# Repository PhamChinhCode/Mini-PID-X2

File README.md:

# Mini PID X2

Board điều khiển 2 động cơ DC chổi than có encoder, chạy vòng PID trên STM32F103C8T6. Thiết kế bằng **KiCad 10**, kích thước **55 × 40 mm**.

## Hình ảnh

| Mặt trên | Mặt dưới |
|---|---|
|  |  |

Mặt dưới có các pad test được in tên: SWD (3V3, DIO, CLK, GND), J8 (5V, CTL1–CTL3, GND) và chân của hai cổng động cơ M1/M2 (OUT1, GND, ENA, ENB, 3V3, OUT2).

## Tính năng

- Điều khiển **2 động cơ DC** bằng 2 × **DRV8871** (H-bridge tích hợp, giới hạn dòng bằng R_ILIM 22 kΩ).
- **2 kênh encoder A/B** với điện trở kéo lên 10 kΩ và bộ lọc RC (1 kΩ + 1 nF).
- MCU **STM32F103C8T6**, thạch anh 16 MHz, USB Full-Speed qua cổng **USB-C**.
- Nguồn vào **VIN** (pin 2S–4S, tối đa khoảng 18 V):
  - Chống cắm ngược cực bằng P-MOSFET **AONR21357**, gate được kẹp bằng Zener 10 V.
  - TVS **SMAJ18A** và tụ hóa 100 µF.
  - Cầu chia đo điện áp VIN đưa về ADC.
- **Buck 5 V MP2359** (1,2 A đỉnh, khuyến nghị tải ≤ 1 A), ghép OR bằng diode với VBUS của USB-C.
- **LDO 3,3 V ME6211** cho MCU và encoder.
- 3 ngõ vào điều khiển ngoài (J8), mỗi ngõ có LED báo trạng thái.
- Cổng UART, I2C và SWD riêng; nút RESET, BOOT0 và USER.

## Cấu trúc thư mục

| Đường dẫn | Nội dung |
|---|---|
| `MiniPID_Manual.kicad_pro` / `.kicad_sch` / `.kicad_pcb` | Project KiCad: schematic và PCB |
| `MiniPID_Manual.kicad_sym` | Thư viện symbol riêng của project (MP2359DJ) |
| `MiniPID_Manual.pretty/` | Thư viện footprint riêng |
| `BOM_MuaHang.csv` | Danh sách mua linh kiện đã gộp mã (32 mã, 89 linh kiện mỗi board), có mã LCSC |
| `bom/ibom.html` | Interactive BOM, mở bằng trình duyệt để hỗ trợ hàn |
| `gerber_to_order/` | Gerber nén zip để đặt mạch (JLCPCB, PCBWay, Elecrow, FusionPCB) |
| `images/` | Ảnh render 3D, mặt trên và mặt dưới của PCB |
| `tools/` | CLI `minipid` bọc `kicad-cli` và `pcbnew` (xem `tools/README.md`) |
| `legacy/` | Dữ liệu gốc từ EasyEDA Pro (file `.epro`, symbol và footprint đã import) |

## Connector

| Ref | Loại | Chân |
|---|---|---|
| J1 | Nguồn vào | 1 GND, 2 VIN |
| J2 / J3 | JST PH 6P, động cơ 1 / 2 | 1 OUT1, 2 GND, 3 ENC_A, 4 ENC_B, 5 +3V3, 6 OUT2 |
| J4 | USB-C | USB 2.0 FS, CC 5,1 kΩ (thiết bị) |
| J5 | PicoBlade 4P, UART | 1 +3V3, 2 TX, 3 RX, 4 GND |
| J6 | PicoBlade 4P, I2C | 1 GND, 2 +3V3, 3 SDA, 4 SCL |
| J7 | Header 2.54 mm 4P, SWD | 1 +3V3, 2 SWDIO, 3 SWCLK, 4 GND |
| J8 | JST PH 5P, điều khiển | 1 +5V, 2 CTL1, 3 CTL2, 4 CTL3, 5 GND |

> Encoder được cấp **3,3 V** từ J2/J3. Encoder Hall loại 5 V cần kiểm tra lại mức điện áp trước khi dùng.

## Mở và xuất file

```bash
kicad MiniPID_Manual.kicad_pro
```

```bash
kicad-cli sch erc MiniPID_Manual.kicad_sch
```

```bash
kicad-cli pcb drc --schematic-parity MiniPID_Manual.kicad_pcb
```

## Ghi chú thiết kế

- Buck đặt R4 = 51 kΩ, R5 = 10 kΩ, cho Vout ≈ 4,94 V. Sau diode OR, rail +5V còn khoảng 4,6 V.
- Đầu ra buck dùng tụ 10 µF 50 V × 2; datasheet MP2359 khuyên khoảng 22 µF.
- MP2359 đang ở trạng thái *Not recommended for new designs* (MPS khuyên chuyển sang MP2331H). Linh kiện vẫn có trên JLCPCB/LCSC: C14259, hoặc bản tương thích MSKSEMI C30197555.
- Gerber trong `gerber_to_order/` được xuất ngày 2026-11-08. Nên xuất lại từ PCB hiện tại trước khi đặt mạch.

## Việc còn tồn

- [ ] Lỗ bắt vít H1–H4 chưa gán net trong schematic (8 lỗi ERC).
- [ ] Đường GND trên F.Cu chạm pad H4 (DRC báo chập mạch và vi phạm khe hở).
- [ ] J1: mã LCSC là XT30PW nhưng footprint đang là terminal Phoenix 5.08 mm. Cần đổi mã LCSC cho đúng loại terminal block.
- [ ] R4 trong schematic/PCB đã đổi giá trị thành 51 kΩ nhưng trường LCSC/MPN vẫn là mã 49.9k (C23184). Mã đúng là C23196 / 0603WAF5102T5E (`BOM_MuaHang.csv` đã sửa).
- [ ] Silkscreen ghi "M1 Brigde" / "M2 Brigde", nên sửa thành "Bridge".

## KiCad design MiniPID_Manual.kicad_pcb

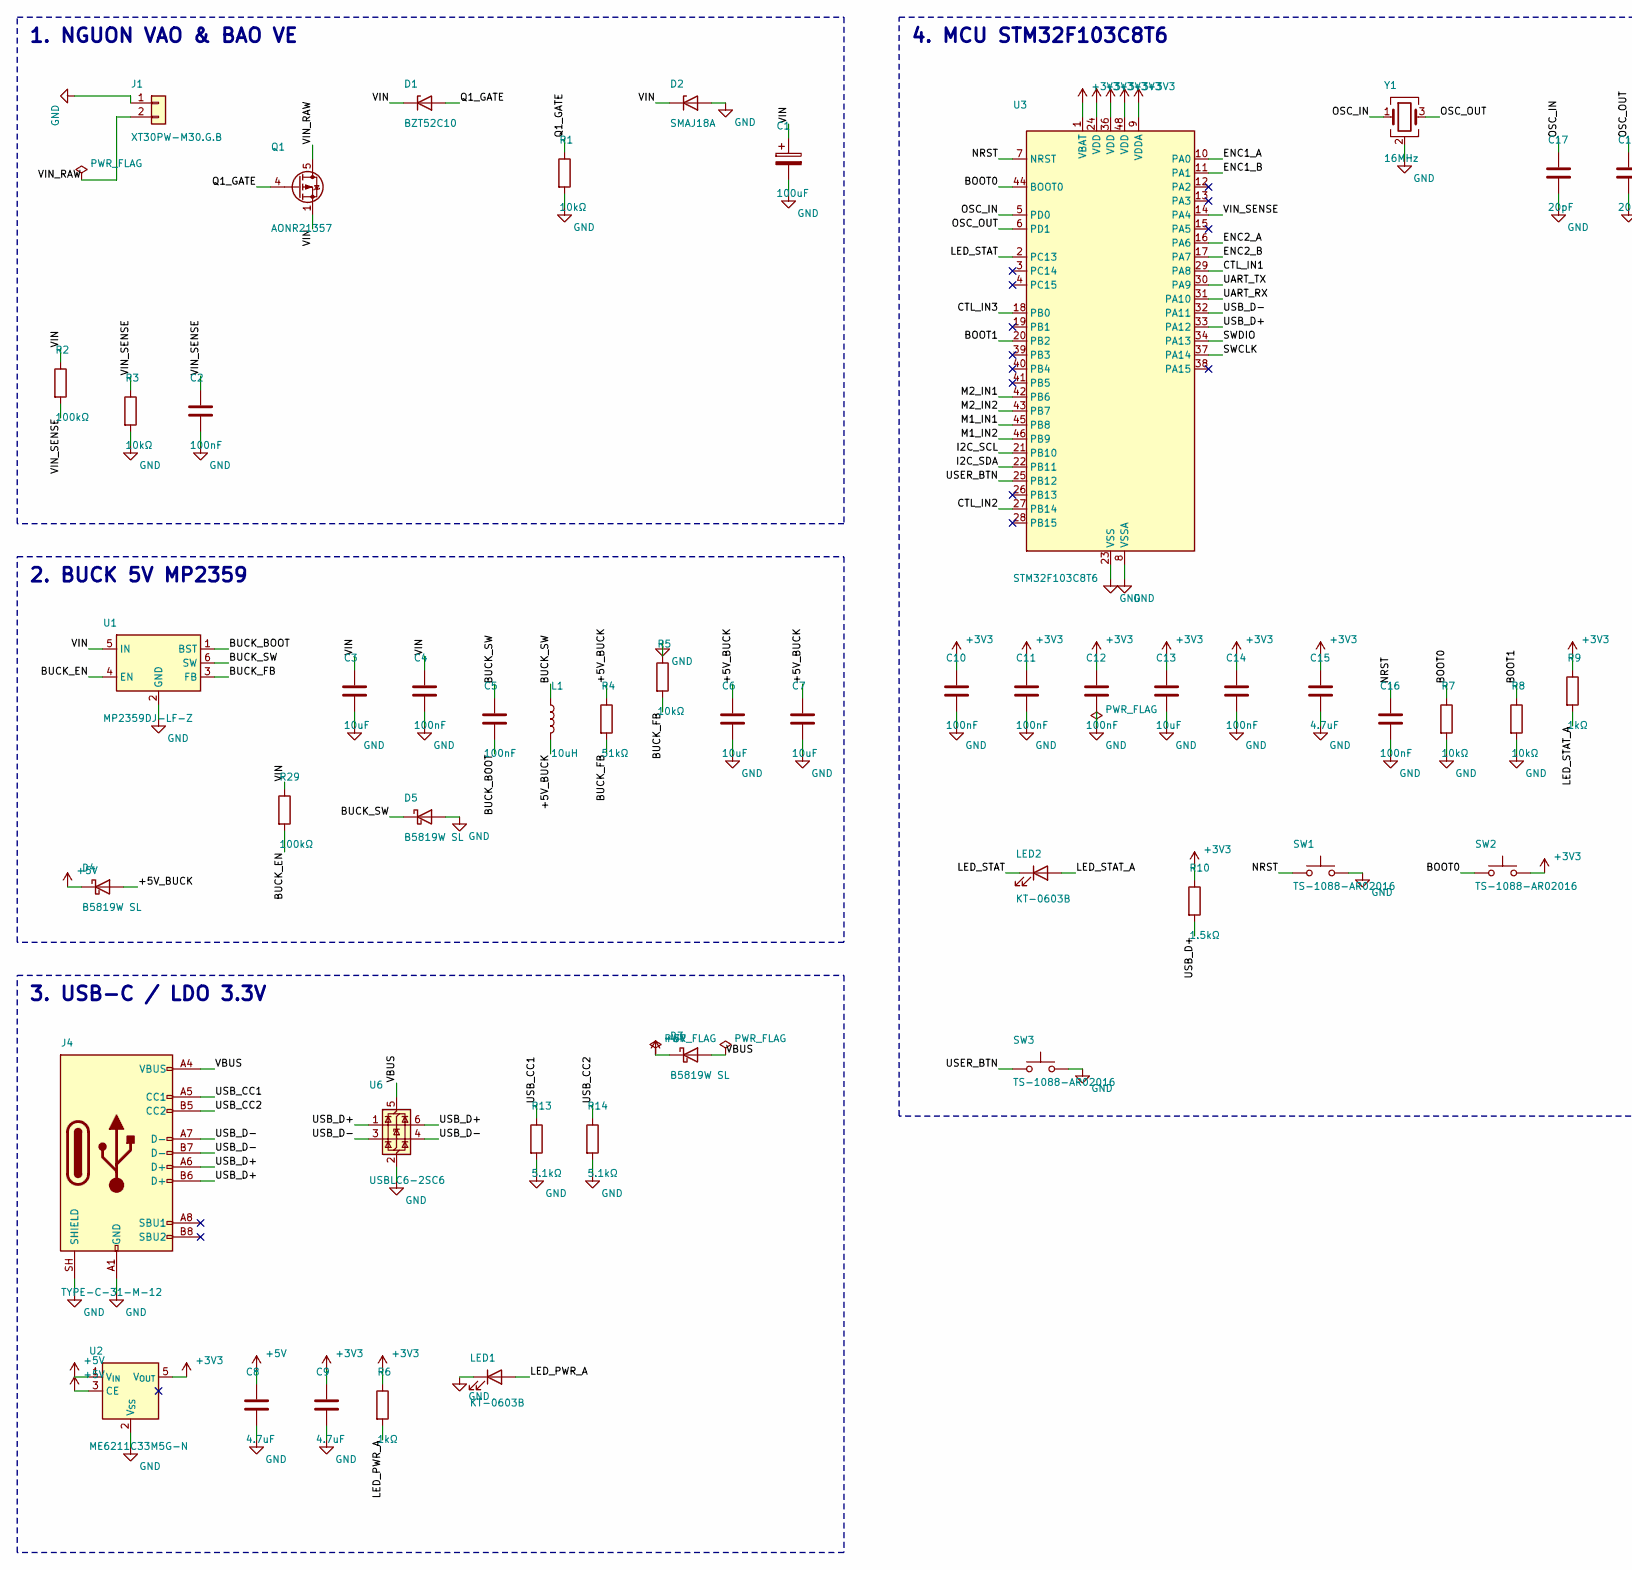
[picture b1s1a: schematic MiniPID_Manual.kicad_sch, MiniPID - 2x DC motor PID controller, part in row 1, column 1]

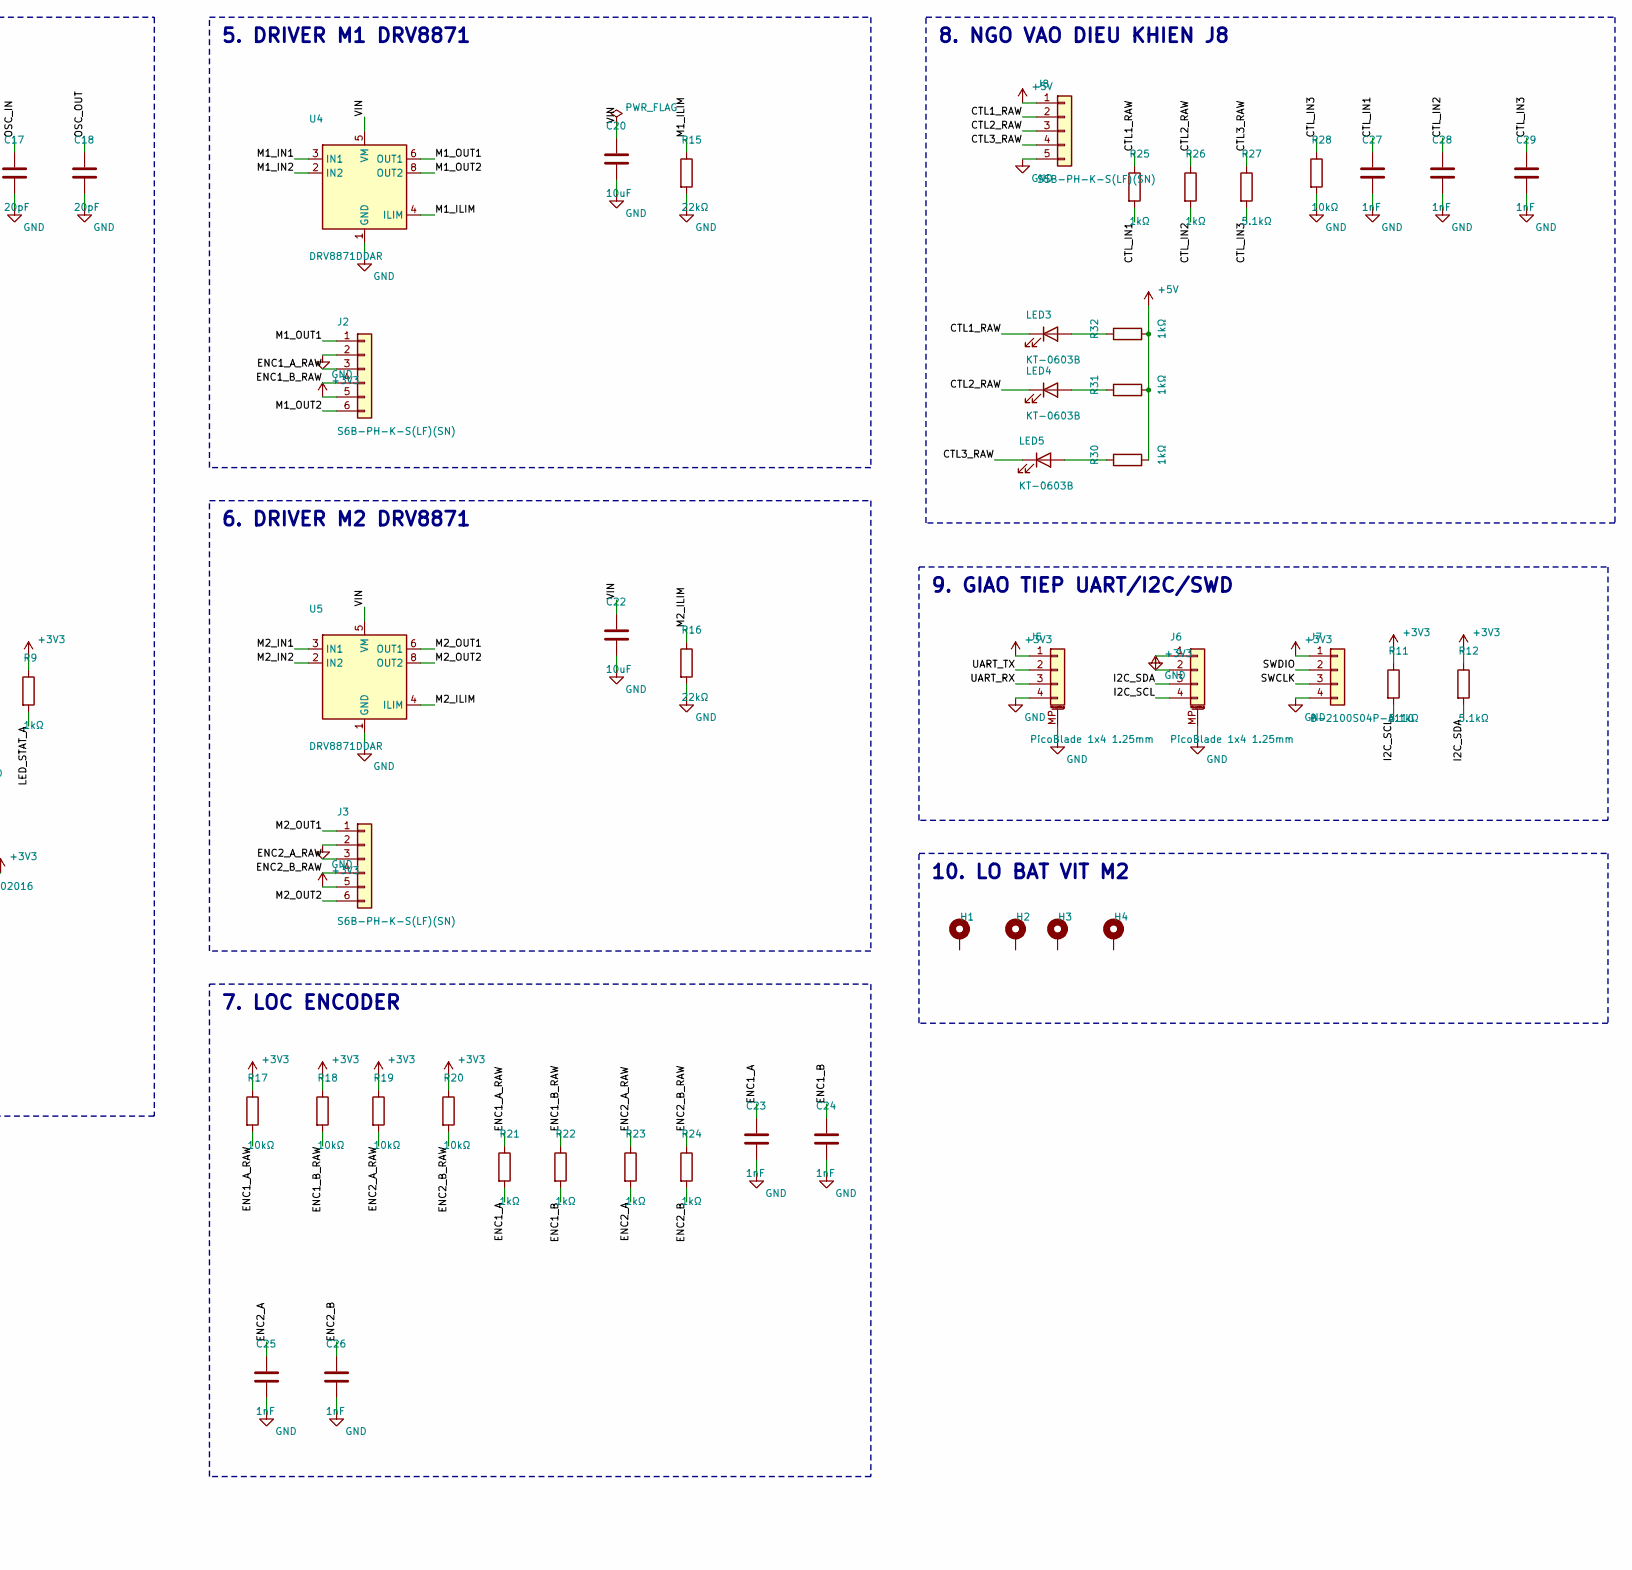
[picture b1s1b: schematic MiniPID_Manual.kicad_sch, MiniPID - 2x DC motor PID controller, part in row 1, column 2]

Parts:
C1: 100uF; CP_Radial_D6.3mm_P2.50mm; MPN NXA35VB100M6.3*11_LO; LCSC C346956
C2, C4, C5, C10, C11, C12, C14, C16: 100nF; C_0603_1608Metric; MPN CC0603KRX7R9BB104; LCSC C14663
C3, C6, C7, C13, C20, C22: 10uF; C_0805_2012Metric; MPN GRM21BR61H106KE43L; LCSC C440198
C8, C9, C15: 4.7uF; C_0603_1608Metric; MPN CL10A475KO8NNNC; LCSC C19666
C17, C18: 20pF; C_0603_1608Metric; MPN CL10C200JB8NNNC; LCSC C1648
C23, C24, C25, C26, C27, C28, C29: 1nF; C_0603_1608Metric; MPN CL10B102KB8NNNC; LCSC C1588
D1: BZT52C10; D_SOD-123; MPN BZT52C10; LCSC C707140
D2: SMAJ18A; D_SMA; MPN SMAJ18A; LCSC C400806
D3, D4, D5: B5819W SL; D_SOD-123; MPN B5819W SL; LCSC C8598
H1, H2, H3, H4: M2; MountingHole_2.2mm_M2_Pad_Via
J1: XT30PW-M30.G.B; TerminalBlock_Phoenix_MKDS-1,5-2-5.08_1x02_P5.08mm_Horizont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; MPN XT30PW-M30.G.B; LCSC C30170177
J2, J3: S6B-PH-K-S(LF)(SN); JST_PH_S6B-PH-K_1x06_P2.00mm_Horizontal; MPN S6B-PH-K-S(LF)(SN); LCSC C157920
J4: TYPE-C-31-M-12; USB_C_Receptacle_HRO_TYPE-C-31-M-12; MPN TYPE-C-31-M-12; LCSC C165948
J5, J6: PicoBlade 1x4 1.25mm; Molex_PicoBlade_53261-0471_1x04-1MP_P1.25mm_Horizontal; MPN 53261-0471; LCSC C240847
J7: B-2100S04P-A110; PinHeader_1x04_P2.54mm_Vertical; MPN B-2100S04P-A110; LCSC C124378
J8: S5B-PH-K-S(LF)(SN); JST_PH_S5B-PH-K_1x05_P2.00mm_Horizontal; MPN S5B-PH-K-S(LF)(SN); LCSC C157923
L1: 10uH; L_Sunlord_SWPA6045S; MPN SWPA6045S100MT; LCSC C79272
LED1, LED2, LED3, LED4, LED5: KT-0603B; LED_0603_1608Metric; MPN KT-0603B; LCSC C2288
Q1: AONR21357; DFN-8-1EP_3x3mm_P0.65mm_EP1.55x2.4mm_EPdrain; MPN AONR21357; LCSC C431196
R1, R3, R5, R7, R8, R17, R18, R19, R20, R28: 10kΩ; R_0603_1608Metric; MPN 0603WAF1002T5E; LCSC C25804
R2, R29: 100kΩ; R_0603_1608Metric; MPN 0603WAF1003T5E; LCSC C25803
R4: 51kΩ; R_0603_1608Metric; MPN 0603WAF4992T5E; LCSC C23184
R6, R9, R21, R22, R23, R24, R25, R26, R30, R31, R32: 1kΩ; R_0603_1608Metric; MPN 0603WAF1001T5E; LCSC C21190
R10: 1.5kΩ; R_0603_1608Metric; MPN 0603WAF1501T5E; LCSC C22843
R11, R12, R13, R14, R27: 5.1kΩ; R_0603_1608Metric; MPN 0603WAF5101T5E; LCSC C23186
R15, R16: 22kΩ; R_0603_1608Metric; MPN 0603WAF2202T5E; LCSC C31850
SW1, SW2, SW3: TS-1088-AR02016; SW_SPST_TS-1088-xR020; MPN TS-1088-AR02016; LCSC C720477
U1: MP2359DJ-LF-Z; TSOT-23-6; MPN MP2359DJ-LF-Z; LCSC C14259
U2: ME6211C33M5G-N; SOT-23-5; MPN ME6211C33M5G-N; LCSC C82942
U3: STM32F103C8T6; LQFP-48_7x7mm_P0.5mm; MPN STM32F103C8T6; LCSC C8734
U4, U5: DRV8871DDAR; Texas_HSOP-8-1EP_3.9x4.9mm_P1.27mm_ThermalVias; MPN DRV8871DDAR; LCSC C75864
U6: USBLC6-2SC6; SOT-23-6; MPN USBLC6-2SC6; LCSC C7519
Y1: 16MHz; Crystal_SMD_3225-4Pin_3.2x2.5mm; MPN X322516MLB4SI; LCSC C13738

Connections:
+3V3: C9.1, C10.1, C11.1, C12.1, C13.1, C14.1, C15.1, J2.5, J3.5, J5.1, J6.2, J7.1, R6.1, R9.1, R10.1, R11.1, R12.1, R17.1, R18.1, R19.1, R20.1, SW2.2, U2.5 (V_{OUT}), U3.1 (VBAT), U3.9 (VDDA), U3.24 (VDD), U3.36 (VDD), U3.48 (VDD)
+5V: C8.1, D3.1 (K), D4.1 (K), J8.1, R30.2, R31.2, R32.2, U2.1 (V_{IN}), U2.3 (CE)
/+5V_BUCK: C6.1, C7.1, D4.2 (A), L1.2, R4.1
/BOOT0: R7.1, SW2.1, U3.44 (BOOT0)
/BOOT1: R8.1, U3.20 (PB2)
/BUCK_BOOT: C5.2, U1.1 (BST)
/BUCK_EN: R29.2, U1.4 (EN)
/BUCK_FB: R4.2, R5.2, U1.3 (FB)
/BUCK_SW: C5.1, D5.1 (K), L1.1, U1.6 (SW)
/CTL1_RAW: J8.2, LED3.1 (K), R25.1
/CTL2_RAW: J8.3, LED4.1 (K), R26.1
/CTL3_RAW: J8.4, LED5.1 (K), R27.1
/CTL_IN1: C27.1, R25.2, U3.29 (PA8)
/CTL_IN2: C28.1, R26.2, U3.27 (PB14)
/CTL_IN3: C29.1, R27.2, R28.1, U3.18 (PB0)
/ENC1_A: C23.1, R21.2, U3.10 (PA0)
/ENC1_A_RAW: J2.3, R17.2, R21.1
/ENC1_B: C24.1, R22.2, U3.11 (PA1)
/ENC1_B_RAW: J2.4, R18.2, R22.1
/ENC2_A: C25.1, R23.2, U3.16 (PA6)
/ENC2_A_RAW: J3.3, R19.2, R23.1
/ENC2_B: C26.1, R24.2, U3.17 (PA7)
/ENC2_B_RAW: J3.4, R20.2, R24.1
/I2C_SCL: J6.4, R11.2, U3.21 (PB10)
/I2C_SDA: J6.3, R12.2, U3.22 (PB11)
/LED_PWR_A: LED1.2 (A), R6.2
/LED_STAT: LED2.1 (K), U3.2 (PC13)
/LED_STAT_A: LED2.2 (A), R9.2
/M1_ILIM: R15.1, U4.4 (ILIM)
/M1_IN1: U3.45 (PB8), U4.3 (IN1)
/M1_IN2: U3.46 (PB9), U4.2 (IN2)
/M1_OUT1: J2.1, U4.6 (OUT1)
/M1_OUT2: J2.6, U4.8 (OUT2)
/M2_ILIM: R16.1, U5.4 (ILIM)
/M2_IN1: U3.42 (PB6), U5.3 (IN1)
/M2_IN2: U3.43 (PB7), U5.2 (IN2)
/M2_OUT1: J3.1, U5.6 (OUT1)
/M2_OUT2: J3.6, U5.8 (OUT2)
/NRST: C16.1, SW1.1, U3.7 (NRST)
/OSC_IN: C17.1, U3.5 (PD0), Y1.1
/OSC_OUT: C18.1, U3.6 (PD1), Y1.3
/Q1_GATE: D1.2 (A), Q1.4 (G), R1.1
/SWCLK: J7.3, U3.37 (PA14)
/SWDIO: J7.2, U3.34 (PA13)
/UART_RX: J5.3, U3.31 (PA10)
/UART_TX: J5.2, U3.30 (PA9)
/USB_CC1: J4.A5 (CC1), R13.1
/USB_CC2: J4.B5 (CC2), R14.1
/USB_D+: J4.A6 (D+), J4.B6 (D+), R10.2, U3.33 (PA12), U6.1 (I/O1), U6.6 (I/O1)
/USB_D-: J4.A7 (D-), J4.B7 (D-), U3.32 (PA11), U6.3 (I/O2), U6.4 (I/O2)
/USER_BTN: SW3.1, U3.25 (PB12)
/VBUS: D3.2 (A), J4.A4 (VBUS), J4.A9 (VBUS), J4.B4 (VBUS), J4.B9 (VBUS), U6.5 (VBUS)
/VIN: C1.1, C3.1, C4.1, C20.1, C22.1, D1.1 (K), D2.1 (K), Q1.1 (S), Q1.2 (S), Q1.3 (S), R2.1, R29.1, U1.5 (IN), U4.5 (VM), U5.5 (VM)
/VIN_RAW: J1.2, Q1.5 (D), Q1.6 (D), Q1.7 (D), Q1.8 (D)
/VIN_SENSE: C2.1, R2.2, R3.1, U3.14 (PA4)
GND: C1.2, C2.2, C3.2, C4.2, C6.2, C7.2, C8.2, C9.2, C10.2, C11.2, C12.2, C13.2, C14.2, C15.2, C16.2, C17.2, C18.2, C20.2, C22.2, C23.2, C24.2, C25.2, C26.2, C27.2, C28.2, C29.2, D2.2 (A), D5.2 (A), J1.1, J2.2, J3.2, J4.A1 (GND), J4.A12 (GND), J4.B1 (GND), J4.B12 (GND), J4.SH (SHIELD), J5.4, J5.MP (MountPin), J6.1, J6.MP (MountPin), J7.4, J8.5, LED1.1 (K), R1.2, R3.2, R5.1, R7.2, R8.2, R13.2, R14.2, R15.2, R16.2, R28.2, SW1.2, SW3.2, U1.2 (GND), U2.2 (V_{SS}), U3.8 (VSSA), U3.23 (VSS), U3.35 (VSS), U3.47 (VSS), U4.1 (GND), U4.7 (GND), U4.9 (GND), U5.1 (GND), U5.7 (GND), U5.9 (GND), U6.2 (GND), Y1.2 (G), Y1.4 (G)
unnamed: LED3.2 (A), R32.1
unnamed: LED4.2 (A), R31.1
unnamed: LED5.2 (A), R30.1

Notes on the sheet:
2. BUCK 5V MP2359
6. DRIVER M2 DRV8871
10. LO BAT VIT M2
4. MCU STM32F103C8T6
9. GIAO TIEP UART/I2C/SWD
8. NGO VAO DIEU KHIEN J8
7. LOC ENCODER
5. DRIVER M1 DRV8871
3. USB-C / LDO 3.3V
1. NGUON VAO & BAO VE

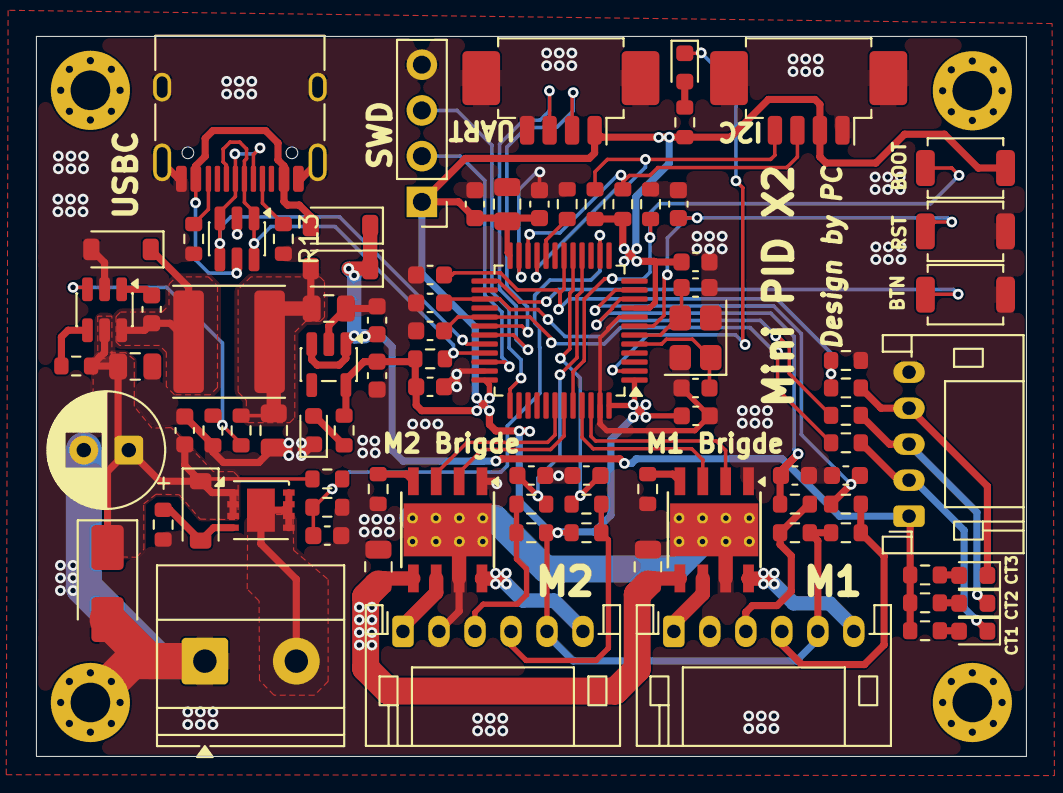
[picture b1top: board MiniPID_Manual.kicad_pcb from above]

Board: 2 copper layers, 55.0 x 40.0 mm, 93 parts (0 on the bottom side), 59 nets.

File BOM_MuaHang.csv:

STT,Nhóm,Giá trị,Kiểu chân,LCSC,MPN,SL/board,Reference,Thay đổi so với schematic
1,Điện trở 0603 1%,10kΩ,0603,C25804,0603WAF1002T5E,10,"R1,R3,R5,R7,R8,R17,R18,R19,R20,R28","R5: 9.53k → 10k (Vout buck ≈ 4,85 V)"
2,Điện trở 0603 1%,100kΩ,0603,C25803,0603WAF1003T5E,2,"R2,R29",
3,Điện trở 0603 1%,51kΩ,0603,C23196,0603WAF5102T5E,1,R4,"49.9k → 51k (Vout buck ≈ 4,94 V)"
4,Điện trở 0603 1%,1kΩ,0603,C21190,0603WAF1001T5E,11,"R6,R9,R21,R22,R23,R24,R25,R26,R30,R31,R32",R21–R24: 100Ω → 1k (lọc encoder fc ≈ 160 kHz)
5,Điện trở 0603 1%,1.5kΩ,0603,C22843,0603WAF1501T5E,1,R10,
6,Điện trở 0603 1%,5.1kΩ,0603,C23186,0603WAF5101T5E,5,"R11,R12,R13,R14,R27","R11,R12: sửa mã LCSC sai (C23162 là 4.7k)"
7,Điện trở 0603 1%,22kΩ,0603,C31850,0603WAF2202T5E,2,"R15,R16",
8,Tụ gốm 0603,100nF 50V X7R,0603,C14663,CC0603KRX7R9BB104,8,"C2,C4,C5,C10,C11,C12,C14,C16",C5 (BST): 10nF → 100nF
9,Tụ gốm 0805,10uF 50V X5R,0805,C440198,GRM21BR61H106KE43L,6,"C3,C6,C7,C13,C20,C22","C6,C7: 22uF/25V → 10uF/50V; C13: sửa mã (C19666 là gói 0603)"
10,Tụ gốm 0603,4.7uF 16V X5R,0603,C19666,CL10A475KO8NNNC,3,"C8,C9,C15","C8,C15: 1uF → 4.7uF"
11,Tụ gốm 0603,1nF 50V X7R,0603,C1588,CL10B102KB8NNNC,7,"C23,C24,C25,C26,C27,C28,C29",
12,Tụ gốm 0603,20pF 50V C0G,0603,C1648,CL10C200JB8NNNC,2,"C17,C18",
13,Tụ hóa,100uF 35V,Radial D6.3 P2.5,C346956,NXA35VB100M6.3*11_LO,1,C1,
14,Diode,B5819W SL (Schottky 40V 1A),SOD-123,C8598,B5819W SL,3,"D3,D4,D5",
15,Diode,BZT52C10 (Zener 10V),SOD-123,C707140,BZT52C10,1,D1,
16,Diode,SMAJ18A (TVS),SMA,C400806,SMAJ18A,1,D2,
17,LED,KT-0603B (xanh dương),0603,C2288,KT-0603B,5,"LED1,LED2,LED3,LED4,LED5",LED1: xanh lá KT-0603G → xanh dương
18,Cuộn cảm,10uH,SWPA6045S,C79272,SWPA6045S100MT,1,L1,
19,MOSFET,AONR21357 (P-ch 30V),DFN-8 3x3,C431196,AONR21357,1,Q1,
20,Connector,XT30PW-M30.G.B,XT30 (kiểm tra footprint!),C30170177,XT30PW-M30.G.B,1,J1,"KIỂM TRA: footprint đang là terminal Phoenix 5.08, không phải XT30"
21,Connector,JST PH 6P ngang,S6B-PH-K,C157920,S6B-PH-K-S(LF)(SN),2,"J2,J3",
22,Connector,USB-C 16P,TYPE-C-31-M-12,C165948,TYPE-C-31-M-12,1,J4,
23,Connector,PicoBlade 4P 1.25mm,53261-0471,C240847,53261-0471,2,"J5,J6",
24,Connector,Header 1x4 2.54mm,PinHeader_1x04,C124378,B-2100S04P-A110,1,J7,
25,Connector,JST PH 5P ngang,S5B-PH-K,C157923,S5B-PH-K-S(LF)(SN),1,J8,
26,Nút nhấn,TS-1088-AR02016,SMD,C720477,TS-1088-AR02016,3,"SW1,SW2,SW3",
27,IC,MP2359DJ-LF-Z (buck 5V),TSOT-23-6,C14259,MP2359DJ-LF-Z,1,U1,
28,IC,ME6211C33M5G-N (LDO 3.3V),SOT-23-5,C82942,ME6211C33M5G-N,1,U2,
29,IC,STM32F103C8T6,LQFP-48,C8734,STM32F103C8T6,1,U3,
30,IC,DRV8871DDAR,HSOP-8,C75864,DRV8871DDAR,2,"U4,U5",
31,IC,USBLC6-2SC6 (ESD USB),SOT-23-6,C7519,USBLC6-2SC6,1,U6,
32,Thạch anh,16MHz,3225 4 chân,C13738,X322516MLB4SI,1,Y1,
